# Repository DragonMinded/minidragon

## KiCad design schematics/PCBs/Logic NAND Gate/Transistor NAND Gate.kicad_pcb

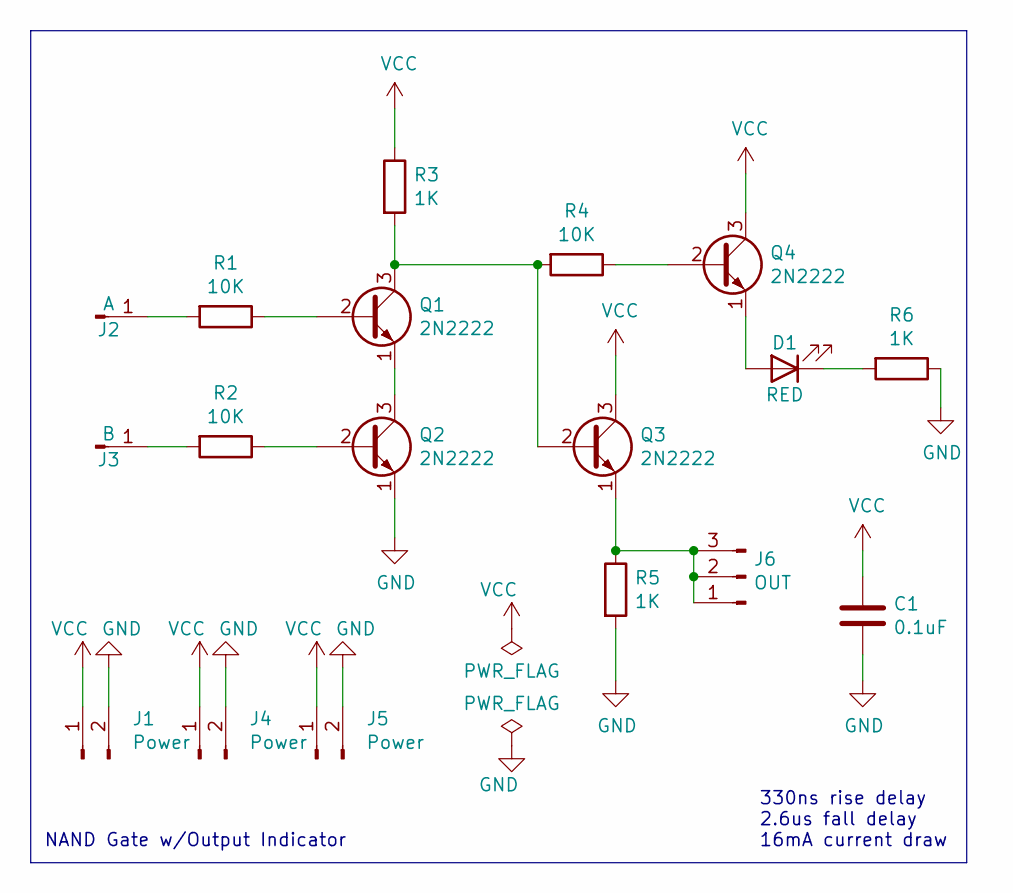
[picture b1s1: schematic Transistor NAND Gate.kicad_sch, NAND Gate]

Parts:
C1: 0.1uF; C_Disc_D4.3mm_W1.9mm_P5.00mm
D1: RED; LED_D5.0mm
J1, J4, J5: Power; PinHeader_1x02_P2.54mm_Vertical
J2: A; PinHeader_1x01_P2.54mm_Vertical
J3: B; PinHeader_1x01_P2.54mm_Vertical
J6: OUT; PinHeader_1x03_P2.54mm_Vertical
Q1, Q2, Q3, Q4: 2N2222; TO-92_Inline
R1, R2, R4: 10K; R_Axial_DIN0309_L9.0mm_D3.2mm_P12.70mm_Horizontal
R3, R5, R6: 1K; R_Axial_DIN0309_L9.0mm_D3.2mm_P12.70mm_Horizontal

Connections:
GND: C1.2, J1.2, J4.2, J5.2, Q2.1 (E), R5.2, R6.1
unnamed: D1.2 (A), Q4.1 (E)
unnamed: D1.1 (K), R6.2
unnamed: J2.1, R1.2
unnamed: J3.1, R2.2
unnamed: J6.1, J6.2, J6.3, Q3.1 (E), R5.1
unnamed: Q1.2 (B), R1.1
unnamed: Q1.3 (C), Q3.2 (B), R3.2, R4.2
unnamed: Q1.1 (E), Q2.3 (C)
unnamed: Q2.2 (B), R2.1
unnamed: Q4.2 (B), R4.1
VCC: C1.1, J1.1, J4.1, J5.1, Q3.3 (C), Q4.3 (C), R3.1

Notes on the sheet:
330ns rise delay 2.6us fall delay 16mA current draw
NAND Gate w/Output Indicator

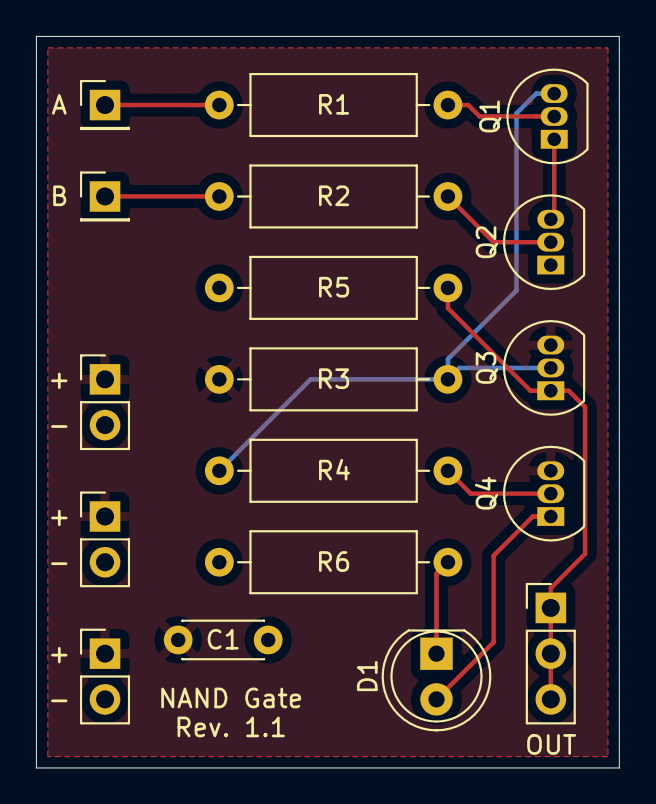
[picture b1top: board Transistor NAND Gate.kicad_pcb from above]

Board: 2 copper layers, 32.4 x 40.6 mm, 18 parts (0 on the bottom side), 12 nets.

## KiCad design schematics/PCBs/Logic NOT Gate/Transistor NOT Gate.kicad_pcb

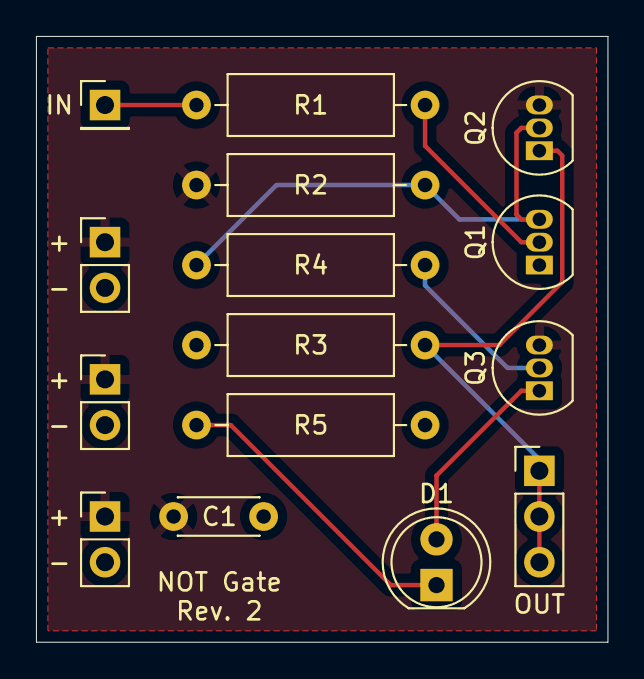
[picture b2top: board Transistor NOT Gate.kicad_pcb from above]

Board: 2 copper layers, 31.8 x 33.7 mm, 15 parts (0 on the bottom side), 9 nets.

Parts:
C1: 0.1uF; C_Disc_D4.3mm_W1.9mm_P5.00mm
D1: RED; LED_D5.0mm
J1: IN; PinHeader_1x01_P2.54mm_Vertical
J2, J3, J4: Power; PinHeader_1x02_P2.54mm_Vertical
J5: OUT; PinHeader_1x03_P2.54mm_Vertical
Q1, Q2, Q3: 2N2222; TO-92_Inline
R1, R4: 10K; R_Axial_DIN0309_L9.0mm_D3.2mm_P12.70mm_Horizontal
R2, R3, R5: 1K; R_Axial_DIN0309_L9.0mm_D3.2mm_P12.70mm_Horizontal

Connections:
GND: C1.2, J2.2, J3.2, J4.2, Q1.1 (E), R3.2, R5.2
unnamed: D1.2 (A), Q3.1 (E)
unnamed: D1.1 (K), R5.1
unnamed: J1.1, R1.2
unnamed: J5.1, J5.2, J5.3, Q2.1 (E), R3.1
unnamed: Q1.2 (B), R1.1
unnamed: Q1.3 (C), Q2.2 (B), R2.2, R4.2
unnamed: Q3.2 (B), R4.1
VCC: C1.1, J2.1, J3.1, J4.1, Q2.3 (C), Q3.3 (C), R2.1

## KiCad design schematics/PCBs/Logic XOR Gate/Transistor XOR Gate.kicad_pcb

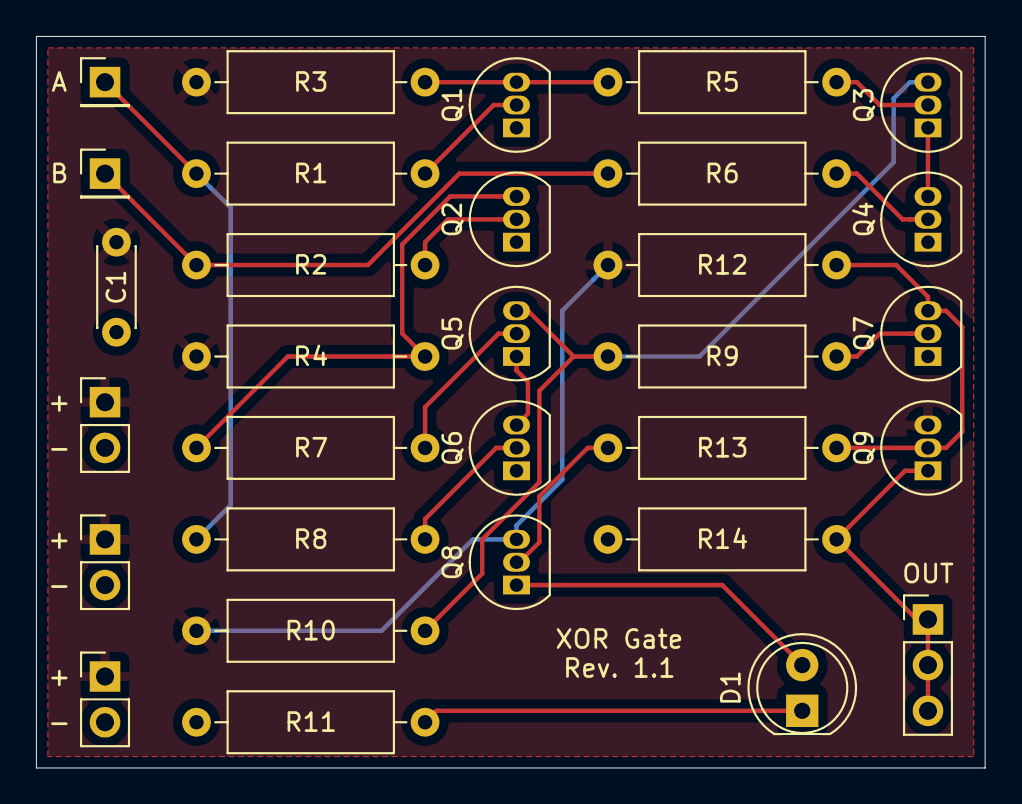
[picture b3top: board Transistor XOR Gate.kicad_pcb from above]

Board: 2 copper layers, 52.7 x 40.6 mm, 31 parts (0 on the bottom side), 21 nets.

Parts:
C1: 0.1uF; C_Disc_D4.3mm_W1.9mm_P5.00mm
D1: LED; LED_D5.0mm
J1: A; PinHeader_1x01_P2.54mm_Vertical
J2: B; PinHeader_1x01_P2.54mm_Vertical
J3, J4, J5: Power; PinHeader_1x02_P2.54mm_Vertical
J6: OUT; PinHeader_1x03_P2.54mm_Vertical
Q1, Q2, Q3, Q4, Q5, Q6, Q7, Q8, Q9: 2N2222; TO-92_Inline
R1, R2, R5, R6, R7, R8, R9, R13: 10K; R_Axial_DIN0309_L9.0mm_D3.2mm_P12.70mm_Horizontal
R3, R4, R10, R11, R12, R14: 1K; R_Axial_DIN0309_L9.0mm_D3.2mm_P12.70mm_Horizontal

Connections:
GND: C1.2, J3.2, J4.2, J5.2, Q1.1 (E), Q2.1 (E), Q4.1 (E), Q6.1 (E), Q7.1 (E), R11.2, R14.1
unnamed: D1.2 (A), Q8.1 (E)
unnamed: D1.1 (K), R11.1
unnamed: J1.1, R1.2, R8.2
unnamed: J2.1, R2.2, R6.2
unnamed: J6.1, J6.2, J6.3, Q9.1 (E), R14.2
unnamed: Q1.2 (B), R1.1
unnamed: Q1.3 (C), R3.2, R5.2
unnamed: Q2.2 (B), R2.1
unnamed: Q2.3 (C), R4.2, R7.2
unnamed: Q3.2 (B), R5.1
unnamed: Q3.3 (C), Q5.3 (C), R9.2, R10.2
unnamed: Q3.1 (E), Q4.3 (C)
unnamed: Q4.2 (B), R6.1
unnamed: Q5.2 (B), R7.1
unnamed: Q5.1 (E), Q6.3 (C)
unnamed: Q6.2 (B), R8.1
unnamed: Q7.2 (B), R9.1
unnamed: Q7.3 (C), Q9.2 (B), R12.1, R13.2
unnamed: Q8.2 (B), R13.1
VCC: C1.1, J3.1, J4.1, J5.1, Q8.3 (C), Q9.3 (C), R3.1, R4.1, R10.1, R12.2
